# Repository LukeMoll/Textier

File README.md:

# Textier
_Low-cost mechanical macro pad_

## Known issues
### "Blackpill" board
 - STM32F411CE only has two USB endpoints - not enough for CircuitPython's MSC & CDC in addition to HID and/or AUDIO (MIDI)
     - Can remove MSC and use [ampy](https://github.com/scientifichackers/ampy) instead
 - Some LED IO shared with optional flash memory footprint
 - Wide DSA profile keycaps conflict with the blackpill board edge when fully inserted in socket
 
Mostly solved by [greenpill](https://github.com/Stary2001/greenpill)

### Blackpill CircuitPython port
 - `rotaryio` [not implemented in STM port](https://github.com/adafruit/circuitpython/issues/2544)
 - `C15` shown as "in use" when try to construct `NeoPixel(board.C15, 9)`

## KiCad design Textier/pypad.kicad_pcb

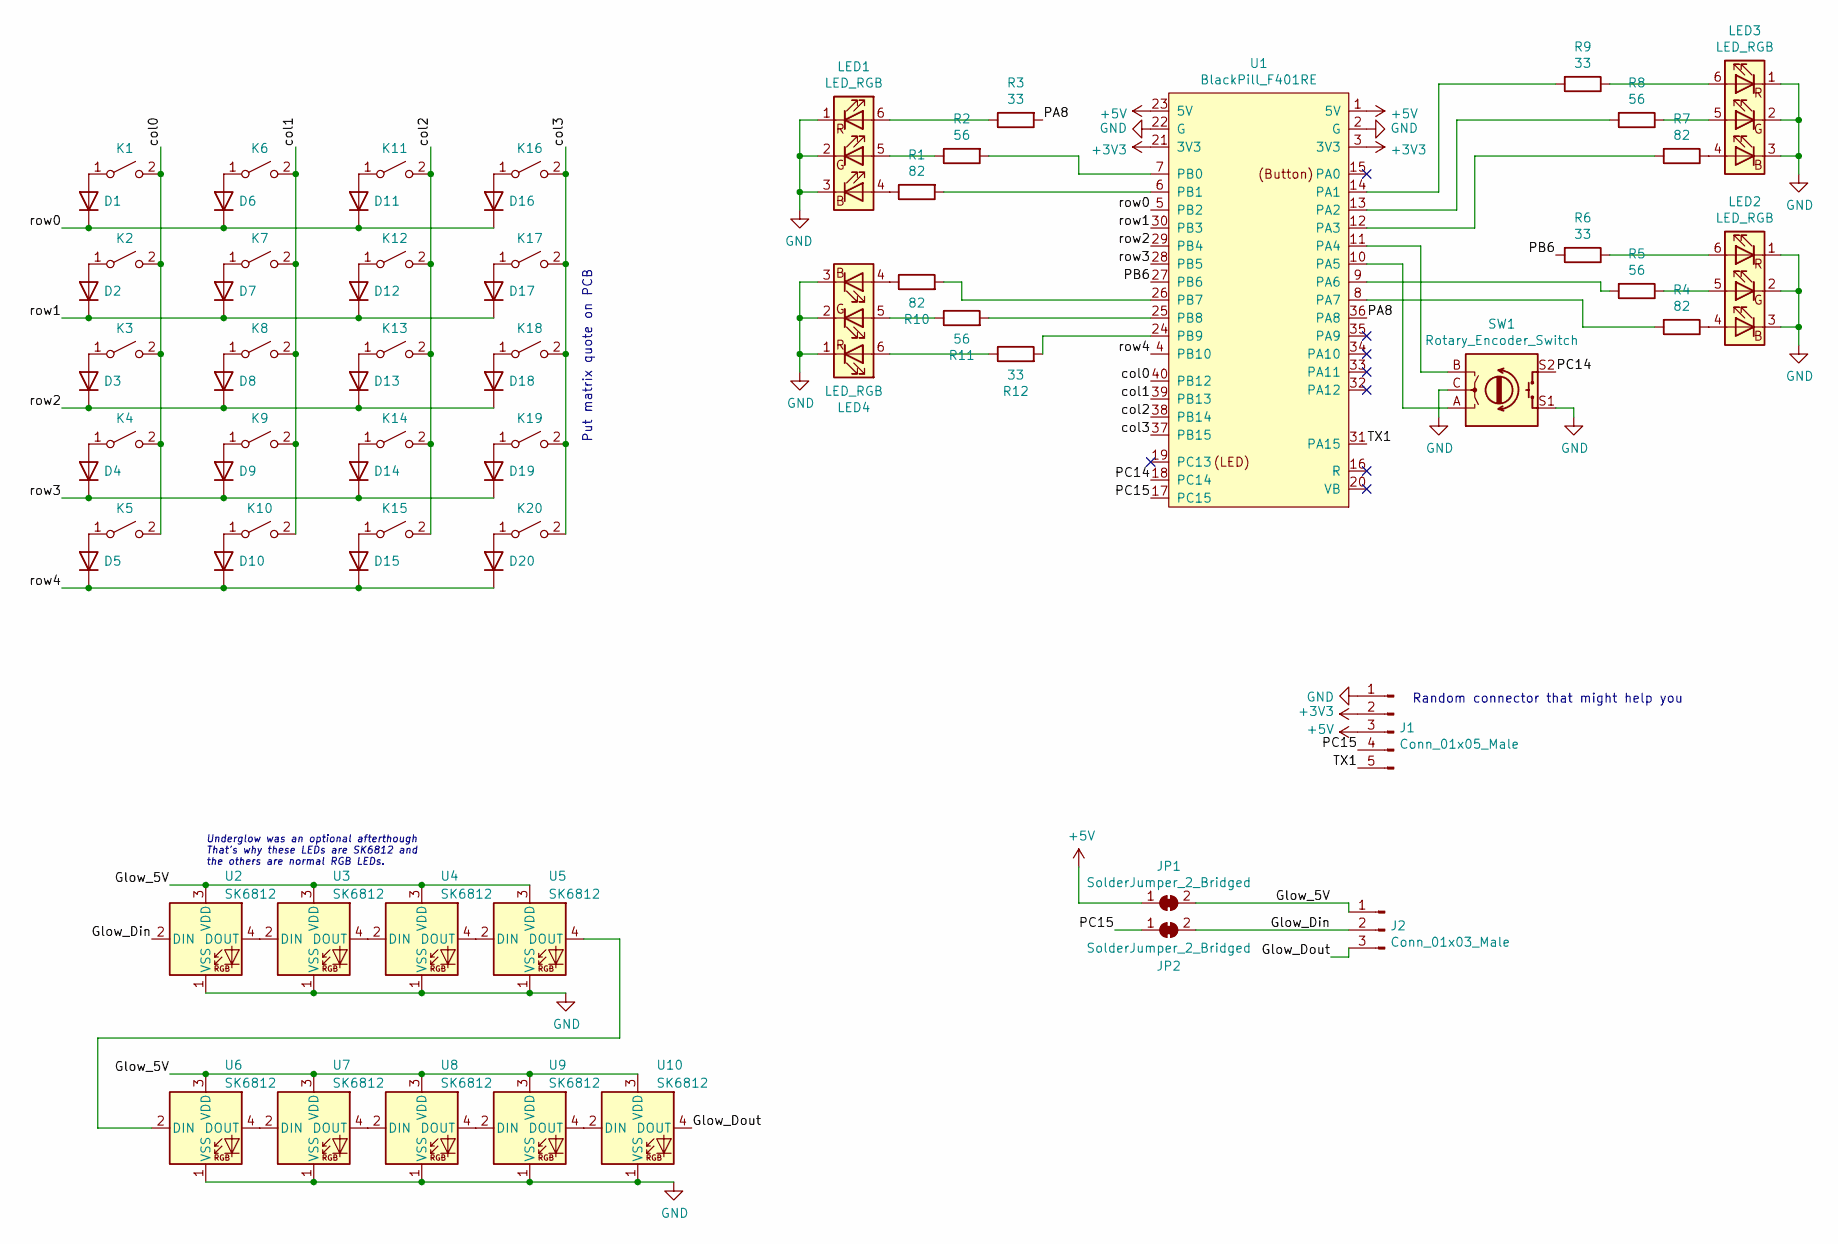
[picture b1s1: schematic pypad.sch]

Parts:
D1, D2, D3, D4, D5, D6, D7, D8, D9, D10, D11, D12, D13, D14, D15, D16, D17, D18, D19, D20: 1N4148; D_DO-35_SOD27_P7.62mm_Horizontal
J1: Conn_01x05_Male; PinHeader_1x05_P2.54mm_Vertical
J2: Conn_01x03_Male; PinHeader_1x03_P2.54mm_Vertical
JP1, JP2: SolderJumper_2_Bridged; SolderJumper-2_P1.3mm_Bridged2BarCuttable_RoundedPad1.0x1.5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
K1, K2, K3, K4, K5, K6, K7, K8, K9, K10, K11, K12, K13, K14, K15, K16, K17, K18, K19, K20: SW_SPST; SW_Cherry_MX_1.00u_PCB
LED1, LED2, LED3, LED4: LED_RGB; LED_RGB_PLCC-6
R1, R4, R7, R10: 82; R_0805_2012Metric_Pad1.15x1.40mm_HandSolder
R2, R5, R8, R11: 56; R_0805_2012Metric_Pad1.15x1.40mm_HandSolder
R3, R6, R9, R12: 33; R_0805_2012Metric_Pad1.15x1.40mm_HandSolder
SW1: Rotary_Encoder_Switch; RotaryEncoder_Bourns_PEC16-4-Switch_Vertical_H20mm
U1: BlackPill_F401RE
U2, U3, U4, U5, U6, U7, U8, U9, U10: SK6812; LED_SK6812_PLCC4_5.0x5.0mm_P3.2mm

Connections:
+3V3: J1.2, U1.3 (3V3), U1.21 (3V3)
+5V: J1.3, JP1.1 (A), U1.1 (5V), U1.23 (5V)
/Glow_5V: J2.1, JP1.2 (B), U2.3 (VDD), U3.3 (VDD), U4.3 (VDD), U5.3 (VDD), U6.3 (VDD), U7.3 (VDD), U8.3 (VDD), U9.3 (VDD), U10.3 (VDD)
/Glow_Din: J2.2, JP2.2 (B), U2.2 (DIN)
/Glow_Dout: J2.3, U10.4 (DOUT)
/PA8: R3.2, U1.36 (PA8)
/PB6: R6.2, U1.27 (PB6)
/PC14: SW1.S2, U1.18 (PC14)
/PC15: J1.4, JP2.1 (A), U1.17 (PC15)
/TX1: J1.5, U1.31 (PA15)
/col0: K1.2 (B), K2.2 (B), K3.2 (B), K4.2 (B), K5.2 (B), U1.40 (PB12)
/col1: K6.2 (B), K7.2 (B), K8.2 (B), K9.2 (B), K10.2 (B), U1.39 (PB13)
/col2: K11.2 (B), K12.2 (B), K13.2 (B), K14.2 (B), K15.2 (B), U1.38 (PB14)
/col3: K16.2 (B), K17.2 (B), K18.2 (B), K19.2 (B), K20.2 (B), U1.37 (PB15)
/row0: D1.1 (K), D6.1 (K), D11.1 (K), D16.1 (K), U1.5 (PB2)
/row1: D2.1 (K), D7.1 (K), D12.1 (K), D17.1 (K), U1.30 (PB3)
/row2: D3.1 (K), D8.1 (K), D13.1 (K), D18.1 (K), U1.29 (PB4)
/row3: D4.1 (K), D9.1 (K), D14.1 (K), D19.1 (K), U1.28 (PB5)
/row4: D5.1 (K), D10.1 (K), D15.1 (K), D20.1 (K), U1.4 (PB10)
GND: J1.1, LED1.1 (RK), LED1.2 (GK), LED1.3 (BK), LED2.1 (RK), LED2.2 (GK), LED2.3 (BK), LED3.1 (RK), LED3.2 (GK), LED3.3 (BK), LED4.1 (RK), LED4.2 (GK), LED4.3 (BK), SW1.C, SW1.S1, U1.2 (G), U1.22 (G), U2.1 (VSS), U3.1 (VSS), U4.1 (VSS), U5.1 (VSS), U6.1 (VSS), U7.1 (VSS), U8.1 (VSS), U9.1 (VSS), U10.1 (VSS)
unnamed: D1.2 (A), K1.1 (A)
unnamed: D2.2 (A), K2.1 (A)
unnamed: D3.2 (A), K3.1 (A)
unnamed: D4.2 (A), K4.1 (A)
unnamed: D5.2 (A), K5.1 (A)
unnamed: D6.2 (A), K6.1 (A)
unnamed: D7.2 (A), K7.1 (A)
unnamed: D8.2 (A), K8.1 (A)
unnamed: D9.2 (A), K9.1 (A)
unnamed: D10.2 (A), K10.1 (A)
unnamed: D11.2 (A), K11.1 (A)
unnamed: D12.2 (A), K12.1 (A)
unnamed: D13.2 (A), K13.1 (A)
unnamed: D14.2 (A), K14.1 (A)
unnamed: D15.2 (A), K15.1 (A)
unnamed: D16.2 (A), K16.1 (A)
unnamed: D17.2 (A), K17.1 (A)
unnamed: D18.2 (A), K18.1 (A)
unnamed: D19.2 (A), K19.1 (A)
unnamed: D20.2 (A), K20.1 (A)
unnamed: LED1.4 (BA), R1.1
unnamed: LED1.5 (GA), R2.1
unnamed: LED1.6 (RA), R3.1
unnamed: LED2.4 (BA), R4.1
unnamed: LED2.5 (GA), R5.1
unnamed: LED2.6 (RA), R6.1
unnamed: LED3.4 (BA), R7.1
unnamed: LED3.5 (GA), R8.1
unnamed: LED3.6 (RA), R9.1
unnamed: LED4.4 (BA), R10.1
unnamed: LED4.5 (GA), R11.1
unnamed: LED4.6 (RA), R12.1
unnamed: R1.2, U1.6 (PB1)
unnamed: R2.2, U1.7 (PB0)
unnamed: R4.2, U1.8 (PA7)
unnamed: R5.2, U1.9 (PA6)
unnamed: R7.2, U1.12 (PA3)
unnamed: R8.2, U1.13 (PA2)
unnamed: R9.2, U1.14 (PA1)
unnamed: R10.2, U1.26 (PB7)
unnamed: R11.2, U1.25 (PB8)
unnamed: R12.2, U1.24 (PB9)
unnamed: SW1.A, U1.10 (PA5)
unnamed: SW1.B, U1.11 (PA4)
unnamed: U2.4 (DOUT), U3.2 (DIN)
unnamed: U3.4 (DOUT), U4.2 (DIN)
unnamed: U4.4 (DOUT), U5.2 (DIN)
unnamed: U5.4 (DOUT), U6.2 (DIN)
unnamed: U6.4 (DOUT), U7.2 (DIN)
unnamed: U7.4 (DOUT), U8.2 (DIN)
unnamed: U8.4 (DOUT), U9.2 (DIN)
unnamed: U9.4 (DOUT), U10.2 (DIN)

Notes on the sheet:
Random connector that might help you
Put matrix quote on PCB
Underglow was an optional afterthough That's why these LEDs are SK6812 and the others are normal RGB LEDs.

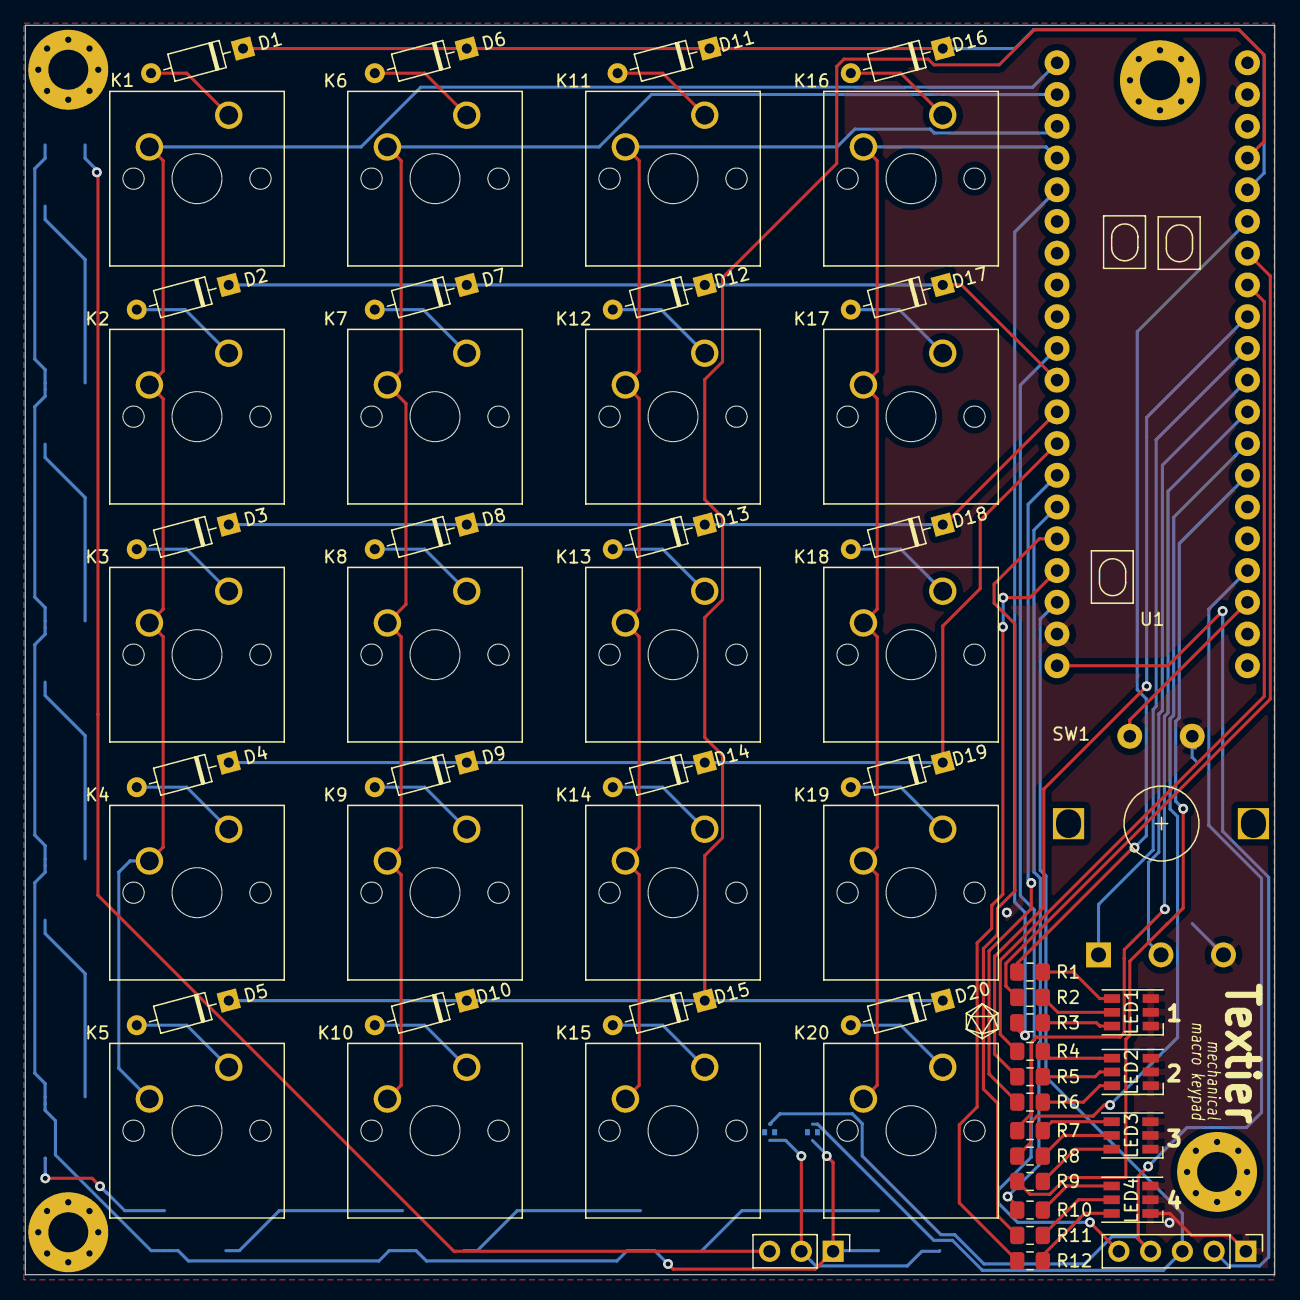
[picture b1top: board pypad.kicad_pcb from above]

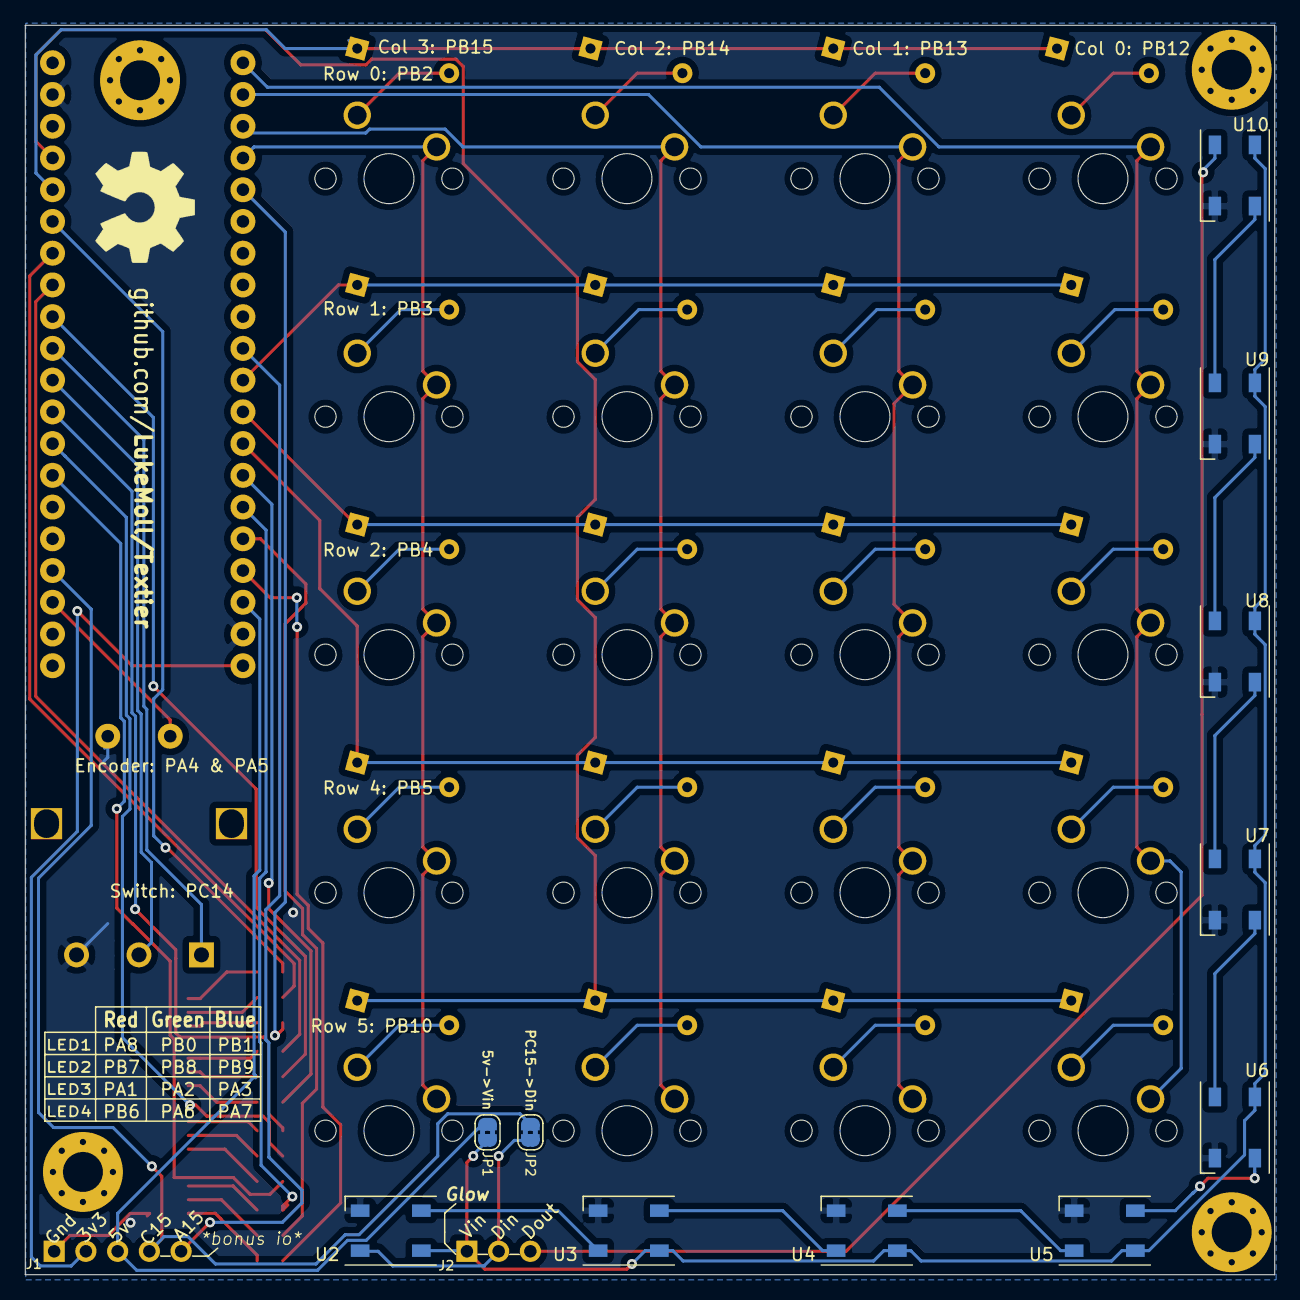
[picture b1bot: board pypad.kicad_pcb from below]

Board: 2 copper layers, 100.0 x 100.0 mm, 75 parts (11 on the bottom side), 72 nets.

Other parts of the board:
M1, M2, M3, M4: MountingHole_3.2mm_M3_Pad_Via

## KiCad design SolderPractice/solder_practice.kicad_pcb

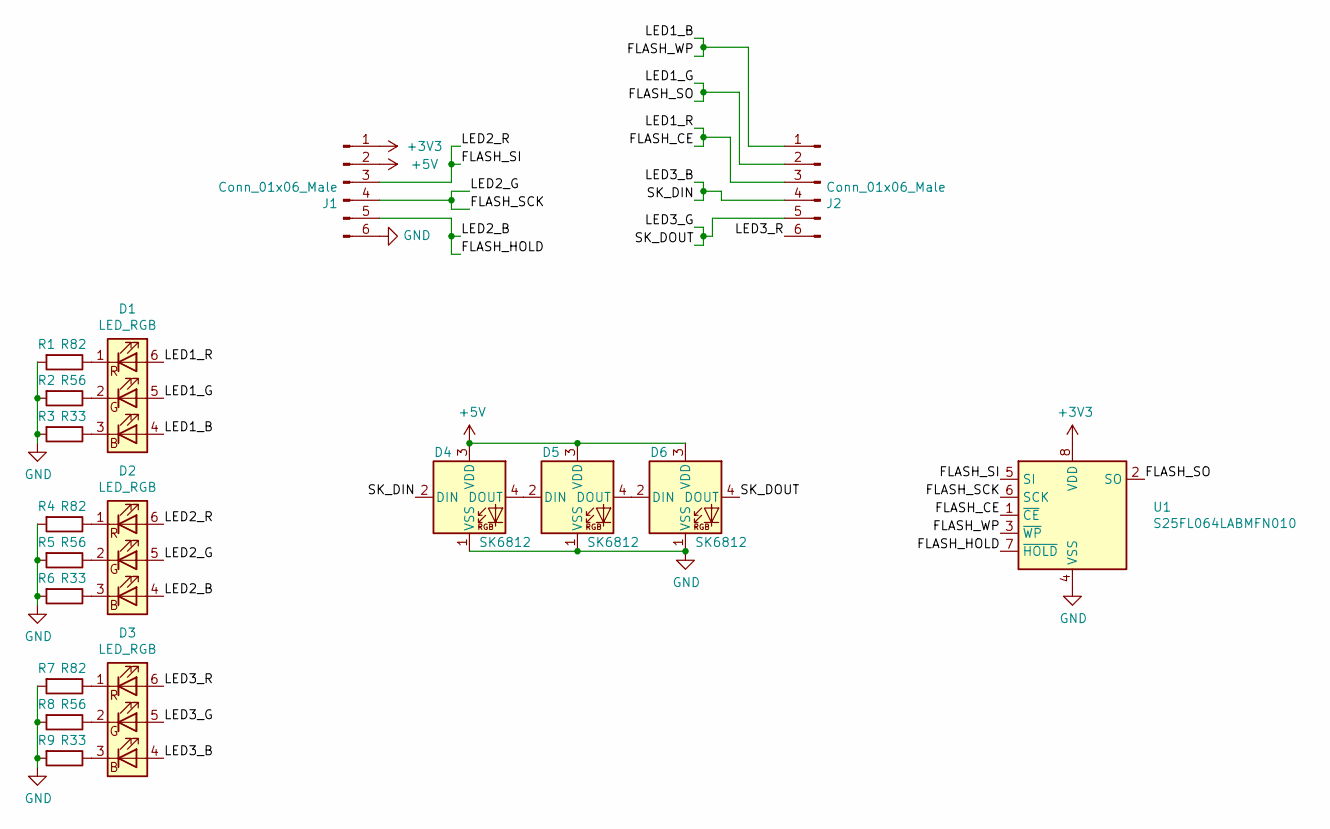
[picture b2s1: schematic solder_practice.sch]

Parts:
D1, D2, D3: LED_RGB; LED_RGB_PLCC-6
D4, D5, D6: SK6812; LED_SK6812_PLCC4_5.0x5.0mm_P3.2mm
J1, J2: Conn_01x06_Male; PinHeader_1x06_P2.54mm_Vertical
R1, R4, R7: R82; R_0805_2012Metric_Pad1.15x1.40mm_HandSolder
R2, R5, R8: R56; R_0805_2012Metric_Pad1.15x1.40mm_HandSolder
R3, R6, R9: R33; R_0805_2012Metric_Pad1.15x1.40mm_HandSolder
U1: S25FL064LABMFN010; SOIC-8_5.275x5.275mm_P1.27mm

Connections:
+3V3: J1.1, U1.8 (VDD)
+5V: D4.3 (VDD), D5.3 (VDD), D6.3 (VDD), J1.2
/FLASH_CE: D1.6 (RA), J2.3, U1.1 (~CE)
/FLASH_HOLD: D2.4 (BA), J1.5, U1.7 (~HOLD~)
/FLASH_SCK: D2.5 (GA), J1.4, U1.6 (SCK)
/FLASH_SI: D2.6 (RA), J1.3, U1.5 (SI)
/FLASH_SO: D1.5 (GA), J2.2, U1.2 (SO)
/FLASH_WP: D1.4 (BA), J2.1, U1.3 (~WP~)
/LED3_B: D3.4 (BA), D4.2 (DIN), J2.4
/LED3_G: D3.5 (GA), D6.4 (DOUT), J2.5
/LED3_R: D3.6 (RA), J2.6
GND: D4.1 (VSS), D5.1 (VSS), D6.1 (VSS), J1.6, R1.2, R2.2, R3.2, R4.2, R5.2, R6.2, R7.2, R8.2, R9.2, U1.4 (VSS)
unnamed: D1.1 (RK), R1.1
unnamed: D1.2 (GK), R2.1
unnamed: D1.3 (BK), R3.1
unnamed: D2.1 (RK), R4.1
unnamed: D2.2 (GK), R5.1
unnamed: D2.3 (BK), R6.1
unnamed: D3.1 (RK), R7.1
unnamed: D3.2 (GK), R8.1
unnamed: D3.3 (BK), R9.1
unnamed: D4.4 (DOUT), D5.2 (DIN)
unnamed: D5.4 (DOUT), D6.2 (DIN)

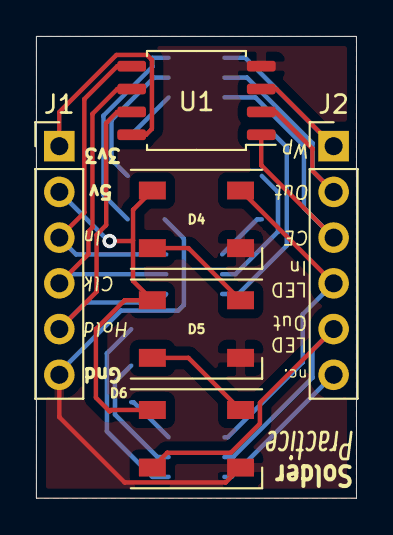
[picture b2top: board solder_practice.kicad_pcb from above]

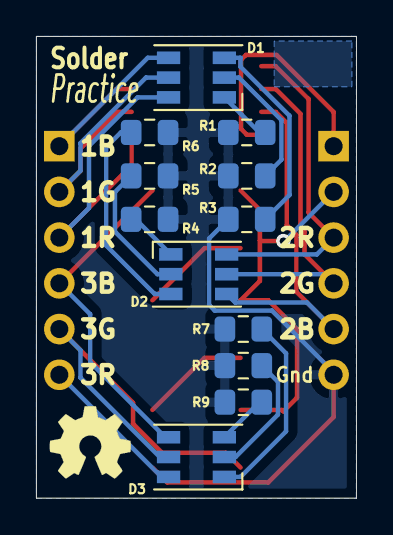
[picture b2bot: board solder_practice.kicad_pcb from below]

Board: 2 copper layers, 17.8 x 25.7 mm, 18 parts (12 on the bottom side), 23 nets.

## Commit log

2020-05-27 Routing attempt number 2
2020-05-28 Revision 2
    Moved board around to allow M3 holes, rerouted using freeRouting and manually fixed.
2020-05-30 Added underglow RGB, misc tweaks
2020-06-01 Revision 3
    Added rotary encoder footprint, reorganised and rerouted board to accommodate.
2020-06-01 Reorganised folder structure
2020-06-01 Added "solder practice" board
2020-06-01 Updated BlackPill footprint
2020-06-01 Feedback fixes
    - OSHW logo + github text
    - removed some leftover silkscreen
2020-07-06 Added README with known issues
